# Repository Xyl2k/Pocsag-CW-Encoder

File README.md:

Pocsag-CW-Encoder
=================

Pocsag / CW Encoder with AVR µC Board layout
Original schematic by N2RVQ can be found here: http://www.dg4has.de/html/pocsac_encoder.html

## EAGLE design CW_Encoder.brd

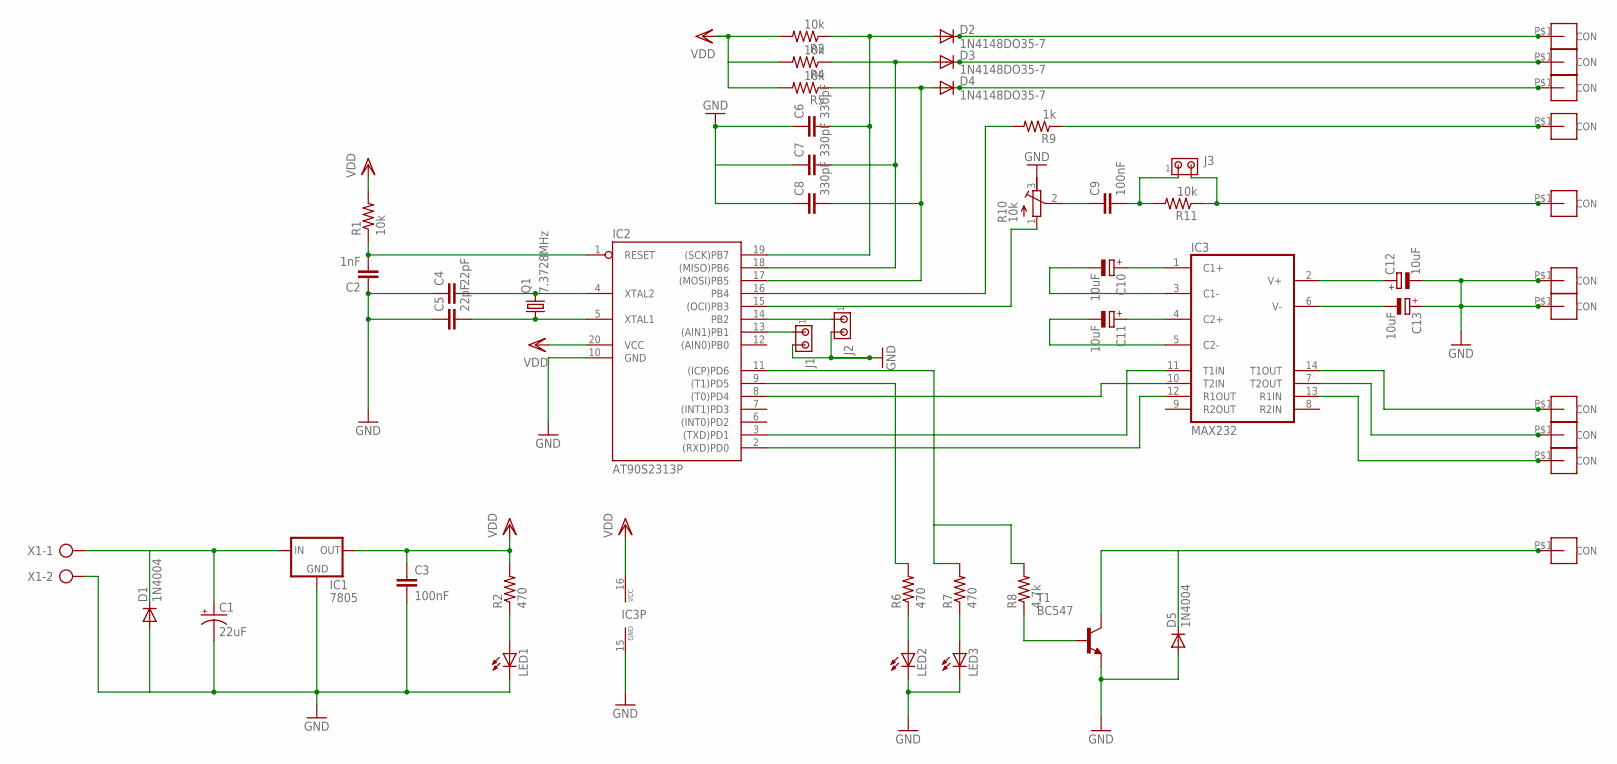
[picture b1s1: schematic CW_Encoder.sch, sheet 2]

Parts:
C1: 22uF; E2,5-4R
C2: 1nF; C025-024X044
C3, C9: 100nF; C025-024X044
C4, C5: 22pF; C025-024X044
C6, C7, C8: 330pF; C025-024X044
C10, C11, C12, C13: 10uF; B45181A
CTS: CON1
CWOUT: CON1
D1, D5: 1N4004; DO41-10
D2, D3, D4: 1N4148DO35-7; DO35-7
GND: CON1
GND_: CON1
IC1: 7805; 78XXL
IC2: AT90S2313P; DIL20
IC3: MAX232; DIL16
IN1, IN2: CON1
J1, J2, J3: MTA02-100; 10X02MTA
LED1, LED2, LED3: LED5MM
POSAGOUT: CON1
PTT: CON1
Q1: 7.3728MHz; HC49/S
R1, R3, R4, R5, R11: 10k; 0204/7
R2, R6, R7: 470; 0204/7
R8: 4.7k; 0204/7
R9: 1k; 0204/7
R10: 10k; RTRIM3339P
T1: BC547; TO92
TX: tx; CON1
TXD: CON1
U$1: CON1
X1: AK300/2

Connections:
GND: C1.-, C2.1, C3.2, C4.1, C5.1, C6.1, C7.1, C8.1, C12.-, C13.+, D1.A, D5.A, GND.P$1, GND_.P$1, IC1.GND, IC2.10 (GND), IC3.15 (GND), J1.2, J2.2, LED1.K (C), LED2.K (C), LED3.K (C), R10.3 (A), T1.1 (E), X1.2
unnamed: C6.2, D2.A, IC2.19 ((SCK)PB7), R3.1
unnamed: LED1.A, R2.1
unnamed: C2.2, IC2.1 (RESET), R1.1
unnamed: C1.+, D1.C, IC1.IN, X1.1
unnamed: C4.2, IC2.4 (XTAL2), Q1.2
unnamed: C5.2, IC2.5 (XTAL1), Q1.1
unnamed: C7.2, D3.A, IC2.18 ((MISO)PB6), R4.1
unnamed: C8.2, D4.A, IC2.17 ((MOSI)PB5), R5.1
unnamed: C10.+, IC3.1 (C1+)
unnamed: C10.-, IC3.3 (C1-)
unnamed: C11.+, IC3.4 (C2+)
unnamed: C11.-, IC3.5 (C2-)
unnamed: C12.+, IC3.2 (V+)
unnamed: C13.-, IC3.6 (V-)
unnamed: LED3.A, R7.1
unnamed: LED2.A, R6.1
unnamed: IC2.9 ((T1)PD5), R6.2
unnamed: IC2.11 ((ICP)PD6), R7.2, R8.2
unnamed: IC2.3 ((TXD)PD1), IC3.11 (T1IN)
unnamed: R8.1, T1.2 (B)
unnamed: IC2.8 ((T0)PD4), IC3.10 (T2IN)
unnamed: IC2.2 ((RXD)PD0), IC3.12 (R1OUT)
unnamed: IC2.15 ((OCI)PB3), R10.1 (E)
unnamed: C9.1, R10.2 (S)
unnamed: C9.2, J3.1, R11.2
unnamed: IC2.16 (PB4), R9.2
unnamed: IC2.14 (PB2), J2.1
unnamed: IC2.13 ((AIN1)PB1), J1.1
unnamed: CWOUT.P$1, J3.2, R11.1
unnamed: D2.C, TX.P$1
unnamed: D3.C, IN1.P$1
unnamed: D4.C, IN2.P$1
unnamed: POSAGOUT.P$1, R9.1
unnamed: IC3.14 (T1OUT), TXD.P$1
unnamed: CTS.P$1, IC3.7 (T2OUT)
unnamed: IC3.13 (R1IN), U$1.P$1
unnamed: D5.C, PTT.P$1, T1.3 (C)
VDD: C3.1, IC1.OUT, IC2.20 (VCC), IC3.16 (VCC), R1.2, R2.2, R3.2, R4.2, R5.2

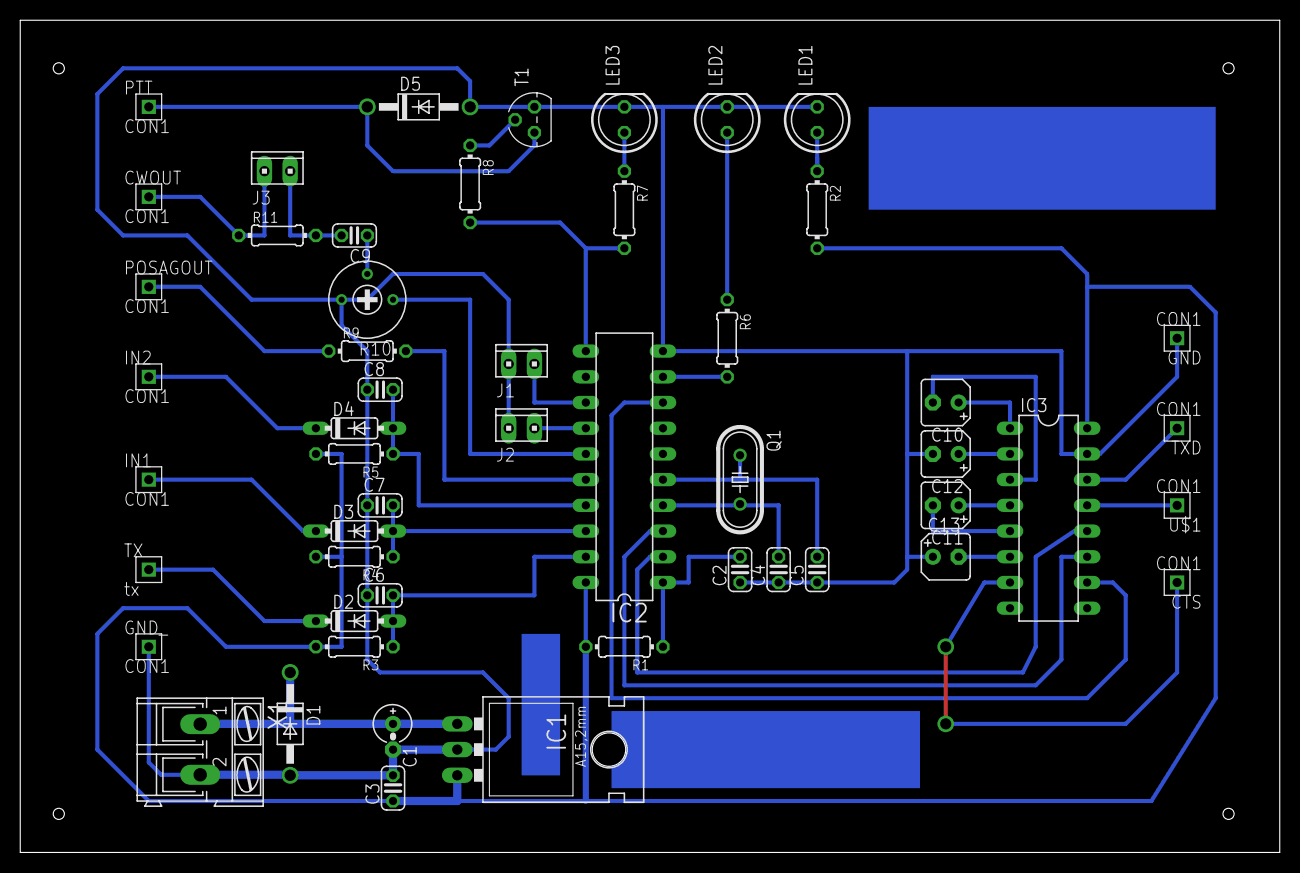
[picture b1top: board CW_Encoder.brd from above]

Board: 2 copper layers, 124.4 x 82.2 mm, 52 parts (0 on the bottom side), 39 nets.

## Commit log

2015-01-03 :space_invader: Added .gitattributes & .gitignore files
2015-01-03 1.0
    1.0
